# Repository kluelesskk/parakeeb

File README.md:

# Parakeeb Keyboard

A staggered, ortholinear board featuring pretty PCB art and a split 50-key
layout.

The board is designed for ProMicro controllers and requires soldering SMD
diodes. It uses Kailh choc switches and their corresponding "narrow" keycap
footprint (i.e. 17.5 x 16.5 mm - standard Cherry spacing of 18 x 18 mm will
not fit).

The board is reversible and switches can be mounted on either side, and/or
the ProMicro can be soldered upside down. A different firmware has to be
flashed depending on the orientation.

## Credits

- The PCB art was produced using [svg2shenzhen](https://github.com/badgeek/svg2shenzhen).
- The PCB was designed with [Kicad](https://kicad.org).
- The artwork was tweaked with [Inkscape](https://inkscape.org).
- The original artwork was found on [SVG Silh](https://svgsilh.com) and is licensed under
  the Creative Commons CC0 license.
- Some PCB components were adapted from the [Keebio parts library](https://github.com/keebio/Keebio-Parts.pretty)
  and are licensed under the MIT license.
- The logo's font was found on [FontSpace](https://www.fontspace.com/mocking-bird-font-f41547)
  and is subject to a non-commercial license.

## License

This project is released under the MIT license.

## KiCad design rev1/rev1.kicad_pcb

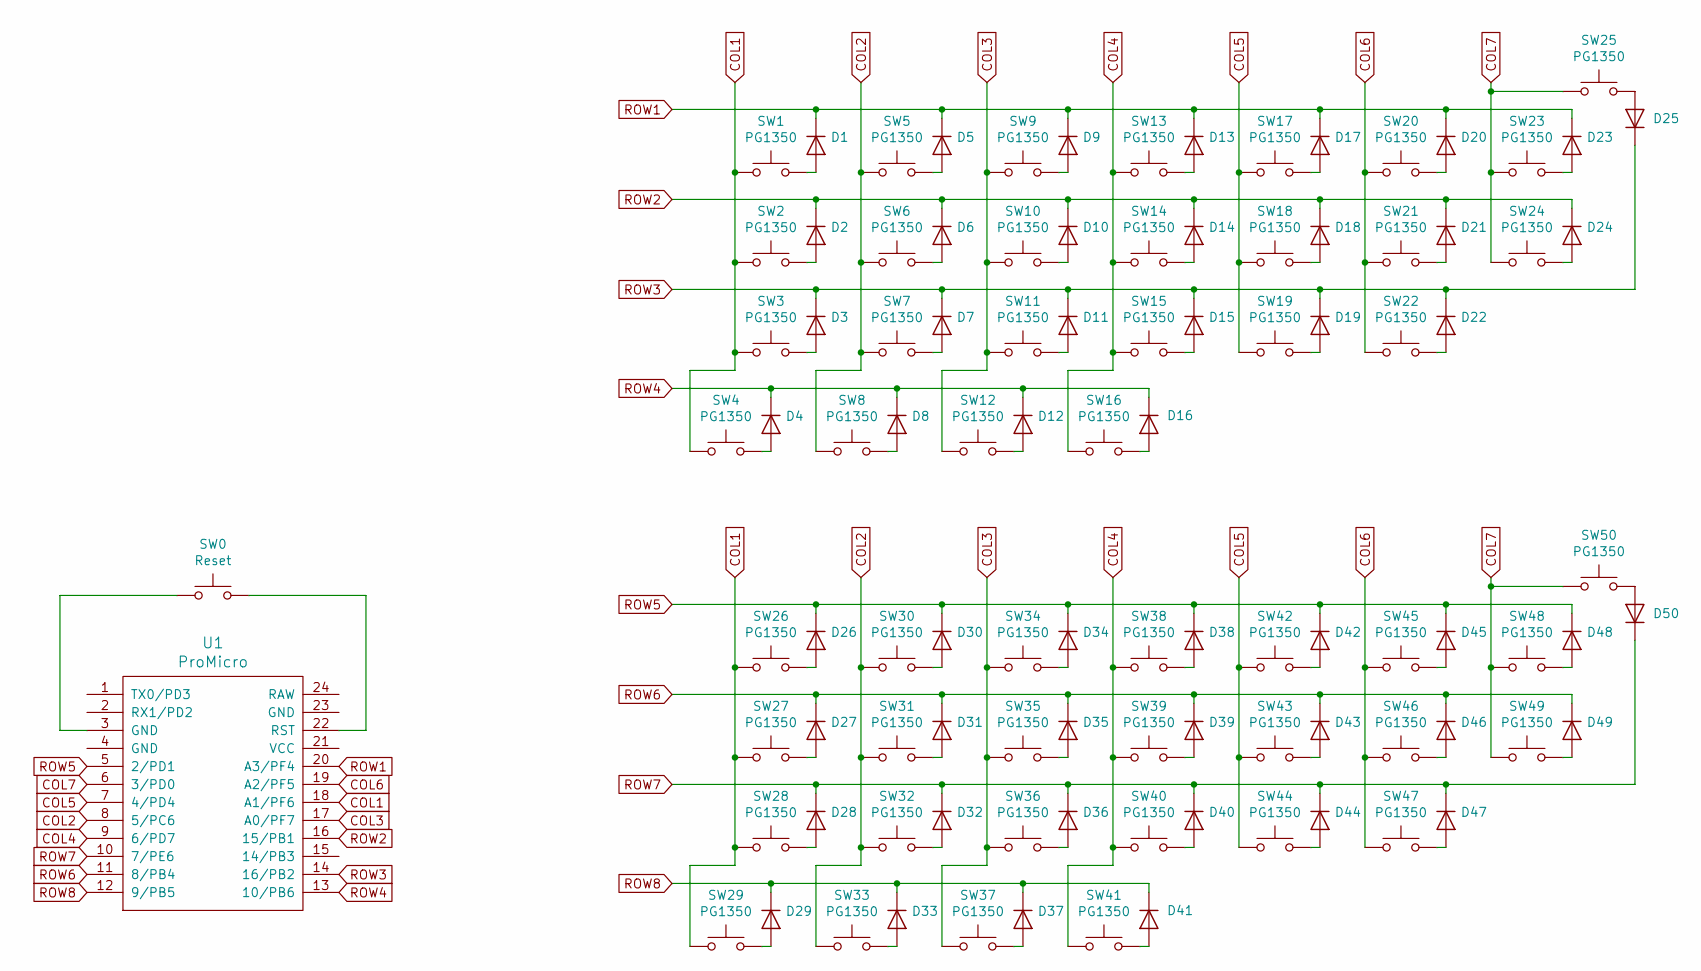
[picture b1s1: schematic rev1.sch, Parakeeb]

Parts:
D1, D2, D3, D4, D5, D6, D7, D8, D9, D10, D11, D12, D13, D14, D15, D16, D17, D18, D19, D20, D21, D22, D23, D24, D25, D26, D27, D28, D29, D30, D31, D32, D33, D34, D35, D36, D37, D38, D39, D40, D41, D42, D43, D44, D45, D46, D47, D48, D49, D50: D_SMB
SW0: Reset; PushButton
SW1, SW2, SW3, SW4, SW5, SW6, SW7, SW8, SW9, SW10, SW11, SW12, SW13, SW14, SW15, SW16, SW17, SW18, SW19, SW20, SW21, SW22, SW23, SW24, SW25, SW26, SW27, SW28, SW29, SW30, SW31, SW32, SW33, SW34, SW35, SW36, SW37, SW38, SW39, SW40, SW41, SW42, SW43, SW44, SW45, SW46, SW47, SW48, SW49, SW50: PG1350; Kailh-PG1350-1u
U1: ProMicro; ArduinoProMicro

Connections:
COL1: SW1.1, SW2.2, SW3.1, SW4.1, SW26.1, SW27.2, SW28.1, SW29.1, U1.18 (A1/PF6)
COL2: SW5.1, SW6.2, SW7.1, SW8.1, SW30.1, SW31.2, SW32.1, SW33.1, U1.8 (5/PC6)
COL3: SW9.1, SW10.2, SW11.1, SW12.1, SW34.1, SW35.2, SW36.1, SW37.1, U1.17 (A0/PF7)
COL4: SW13.1, SW14.2, SW15.1, SW16.1, SW38.1, SW39.2, SW40.1, SW41.1, U1.9 (6/PD7)
COL5: SW17.1, SW18.1, SW19.1, SW42.1, SW43.1, SW44.1, U1.7 (4/PD4)
COL6: SW20.1, SW21.1, SW22.1, SW45.1, SW46.1, SW47.1, U1.19 (A2/PF5)
COL7: SW23.1, SW24.1, SW25.1, SW48.1, SW49.1, SW50.1, U1.6 (3/PD0)
unnamed: D1.2 (A), SW1.2
unnamed: D2.2 (A), SW2.1
unnamed: D3.2 (A), SW3.2
unnamed: D4.2 (A), SW4.2
unnamed: D5.2 (A), SW5.2
unnamed: D6.2 (A), SW6.1
unnamed: D7.2 (A), SW7.2
unnamed: D8.2 (A), SW8.2
unnamed: D9.2 (A), SW9.2
unnamed: D10.2 (A), SW10.1
unnamed: D11.2 (A), SW11.2
unnamed: D12.2 (A), SW12.2
unnamed: D13.2 (A), SW13.2
unnamed: D14.2 (A), SW14.1
unnamed: D15.2 (A), SW15.2
unnamed: D16.2 (A), SW16.2
unnamed: D17.2 (A), SW17.2
unnamed: D18.2 (A), SW18.2
unnamed: D19.2 (A), SW19.2
unnamed: D20.2 (A), SW20.2
unnamed: D21.2 (A), SW21.2
unnamed: D22.2 (A), SW22.2
unnamed: D23.2 (A), SW23.2
unnamed: D24.2 (A), SW24.2
unnamed: D25.2 (A), SW25.2
unnamed: D26.2 (A), SW26.2
unnamed: D27.2 (A), SW27.1
unnamed: D28.2 (A), SW28.2
unnamed: D29.2 (A), SW29.2
unnamed: D30.2 (A), SW30.2
unnamed: D31.2 (A), SW31.1
unnamed: D32.2 (A), SW32.2
unnamed: D33.2 (A), SW33.2
unnamed: D34.2 (A), SW34.2
unnamed: D35.2 (A), SW35.1
unnamed: D36.2 (A), SW36.2
unnamed: D37.2 (A), SW37.2
unnamed: D38.2 (A), SW38.2
unnamed: D39.2 (A), SW39.1
unnamed: D40.2 (A), SW40.2
unnamed: D41.2 (A), SW41.2
unnamed: D42.2 (A), SW42.2
unnamed: D43.2 (A), SW43.2
unnamed: D44.2 (A), SW44.2
unnamed: D45.2 (A), SW45.2
unnamed: D46.2 (A), SW46.2
unnamed: D47.2 (A), SW47.2
unnamed: D48.2 (A), SW48.2
unnamed: D49.2 (A), SW49.2
unnamed: D50.2 (A), SW50.2
unnamed: SW0.1, U1.3 (GND)
unnamed: SW0.2, U1.22 (RST)
ROW1: D1.1 (K), D5.1 (K), D9.1 (K), D13.1 (K), D17.1 (K), D20.1 (K), D23.1 (K), U1.20 (A3/PF4)
ROW2: D2.1 (K), D6.1 (K), D10.1 (K), D14.1 (K), D18.1 (K), D21.1 (K), D24.1 (K), U1.16 (15/PB1)
ROW3: D3.1 (K), D7.1 (K), D11.1 (K), D15.1 (K), D19.1 (K), D22.1 (K), D25.1 (K), U1.14 (16/PB2)
ROW4: D4.1 (K), D8.1 (K), D12.1 (K), D16.1 (K), U1.13 (10/PB6)
ROW5: D26.1 (K), D30.1 (K), D34.1 (K), D38.1 (K), D42.1 (K), D45.1 (K), D48.1 (K), U1.5 (2/PD1)
ROW6: D27.1 (K), D31.1 (K), D35.1 (K), D39.1 (K), D43.1 (K), D46.1 (K), D49.1 (K), U1.11 (8/PB4)
ROW7: D28.1 (K), D32.1 (K), D36.1 (K), D40.1 (K), D44.1 (K), D47.1 (K), D50.1 (K), U1.10 (7/PE6)
ROW8: D29.1 (K), D33.1 (K), D37.1 (K), D41.1 (K), U1.12 (9/PB5)

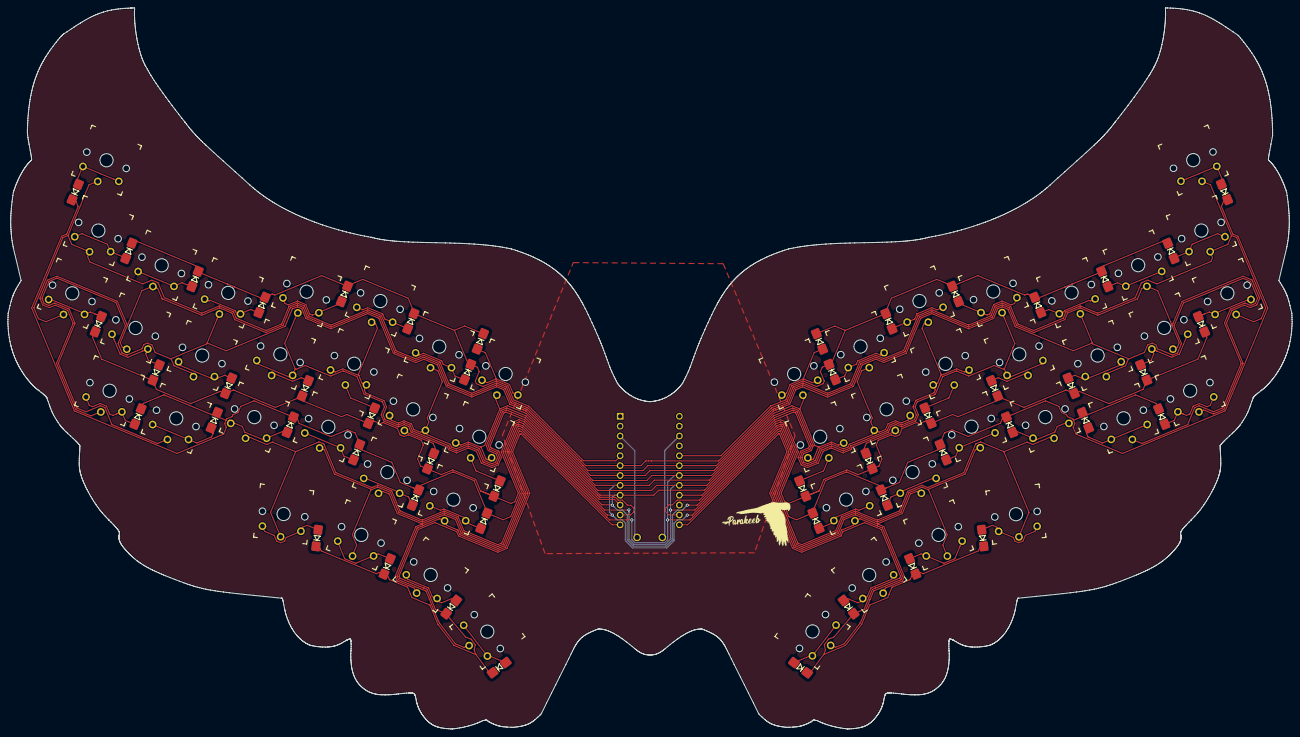
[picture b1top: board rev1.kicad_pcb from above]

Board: 2 copper layers, 330.6 x 185.6 mm, 103 parts (0 on the bottom side), 67 nets.

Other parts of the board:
Ref**: Val**; KeyboardDesign

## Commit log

2021-03-02 Add pcb v1.1
2021-03-02 Add artwork
2021-03-02 Add readme
